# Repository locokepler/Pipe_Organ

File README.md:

# Pipe_Organ
The repository of the code of the pipe organ, over the different iterations

Here is the pipe organ playing Bach's Passacaglia and Fugue in C minor: https://youtu.be/gpJCPvgH33w

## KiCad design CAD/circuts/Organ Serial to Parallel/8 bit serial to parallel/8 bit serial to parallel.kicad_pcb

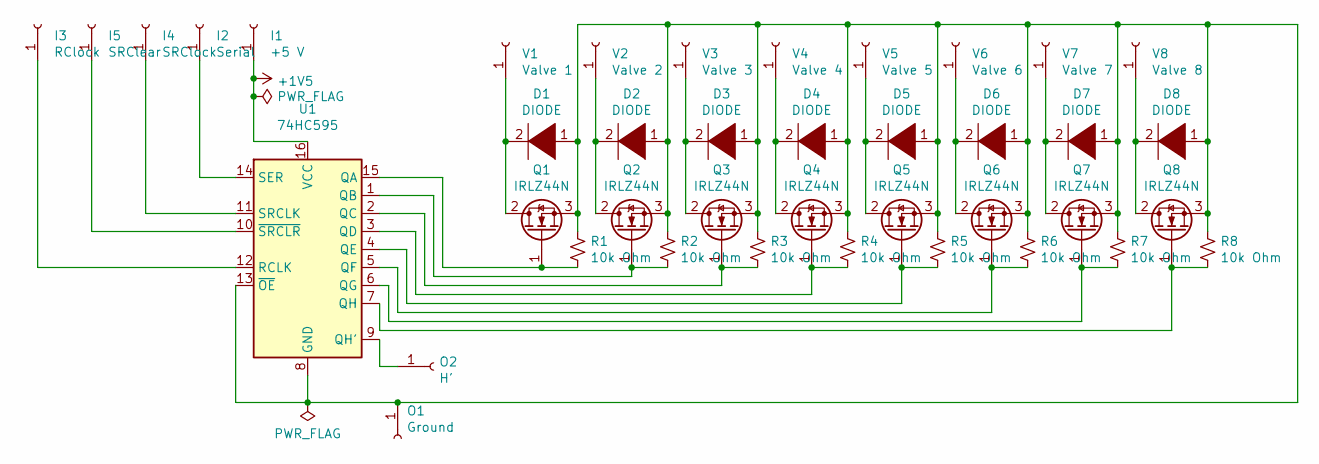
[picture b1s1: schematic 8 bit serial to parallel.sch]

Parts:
D1, D2, D3, D4, D5, D6, D7, D8: DIODE; D_DO-15_P3.81mm_Vertical_AnodeUp
I1: +5 V; SolderWirePad_1x01_Drill2.5mm
I2: Serial; SolderWirePad_1x01_Drill2.5mm
I3: RClock; SolderWirePad_1x01_Drill2.5mm
I4: SRClock; SolderWirePad_1x01_Drill2.5mm
I5: SRClear; SolderWirePad_1x01_Drill2.5mm
O1: Ground; SolderWirePad_1x01_Drill2.5mm
O2: H'; SolderWirePad_1x01_Drill2.5mm
Q1, Q2, Q3, Q4, Q5, Q6, Q7, Q8: IRLZ44N; TO-220-3_Vertical
R1, R2, R3, R4, R5, R6, R7, R8: 10k Ohm; R_Axial_DIN0204_L3.6mm_D1.6mm_P7.62mm_Horizontal
U1: 74HC595; DIP-16_W7.62mm
V1: Valve 1; SolderWirePad_1x01_Drill2.5mm
V2: Valve 2; SolderWirePad_1x01_Drill2.5mm
V3: Valve 3; SolderWirePad_1x01_Drill2.5mm
V4: Valve 4; SolderWirePad_1x01_Drill2.5mm
V5: Valve 5; SolderWirePad_1x01_Drill2.5mm
V6: Valve 6; SolderWirePad_1x01_Drill2.5mm
V7: Valve 7; SolderWirePad_1x01_Drill2.5mm
V8: Valve 8; SolderWirePad_1x01_Drill2.5mm

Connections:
+1V5: I1.1, U1.16 (VCC)
unnamed: D1.1 (K), D2.1 (K), D3.1 (K), D4.1 (K), D5.1 (K), D6.1 (K), D7.1 (K), D8.1 (K), O1.1, Q1.3 (S), Q2.3 (S), Q3.3 (S), Q4.3 (S), Q5.3 (S), Q6.3 (S), Q7.3 (S), Q8.3 (S), R1.1, R2.1, R3.1, R4.1, R5.1, R6.1, R7.1, R8.1, U1.8 (GND), U1.13 (~OE)
unnamed: D1.2 (A), Q1.2 (D), V1.1
unnamed: D2.2 (A), Q2.2 (D), V2.1
unnamed: D3.2 (A), Q3.2 (D), V3.1
unnamed: D4.2 (A), Q4.2 (D), V4.1
unnamed: D5.2 (A), Q5.2 (D), V5.1
unnamed: D6.2 (A), Q6.2 (D), V6.1
unnamed: D7.2 (A), Q7.2 (D), V7.1
unnamed: D8.2 (A), Q8.2 (D), V8.1
unnamed: I2.1, U1.14 (SER)
unnamed: I3.1, U1.12 (RCLK)
unnamed: I4.1, U1.11 (SRCLK)
unnamed: I5.1, U1.10 (~SRCLR)
unnamed: O2.1, U1.9 (QH')
unnamed: Q1.1 (G), R1.2, U1.15 (QA)
unnamed: Q2.1 (G), R2.2, U1.1 (QB)
unnamed: Q3.1 (G), R3.2, U1.2 (QC)
unnamed: Q4.1 (G), R4.2, U1.3 (QD)
unnamed: Q5.1 (G), R5.2, U1.4 (QE)
unnamed: Q6.1 (G), R6.2, U1.5 (QF)
unnamed: Q7.1 (G), R7.2, U1.6 (QG)
unnamed: Q8.1 (G), R8.2, U1.7 (QH)

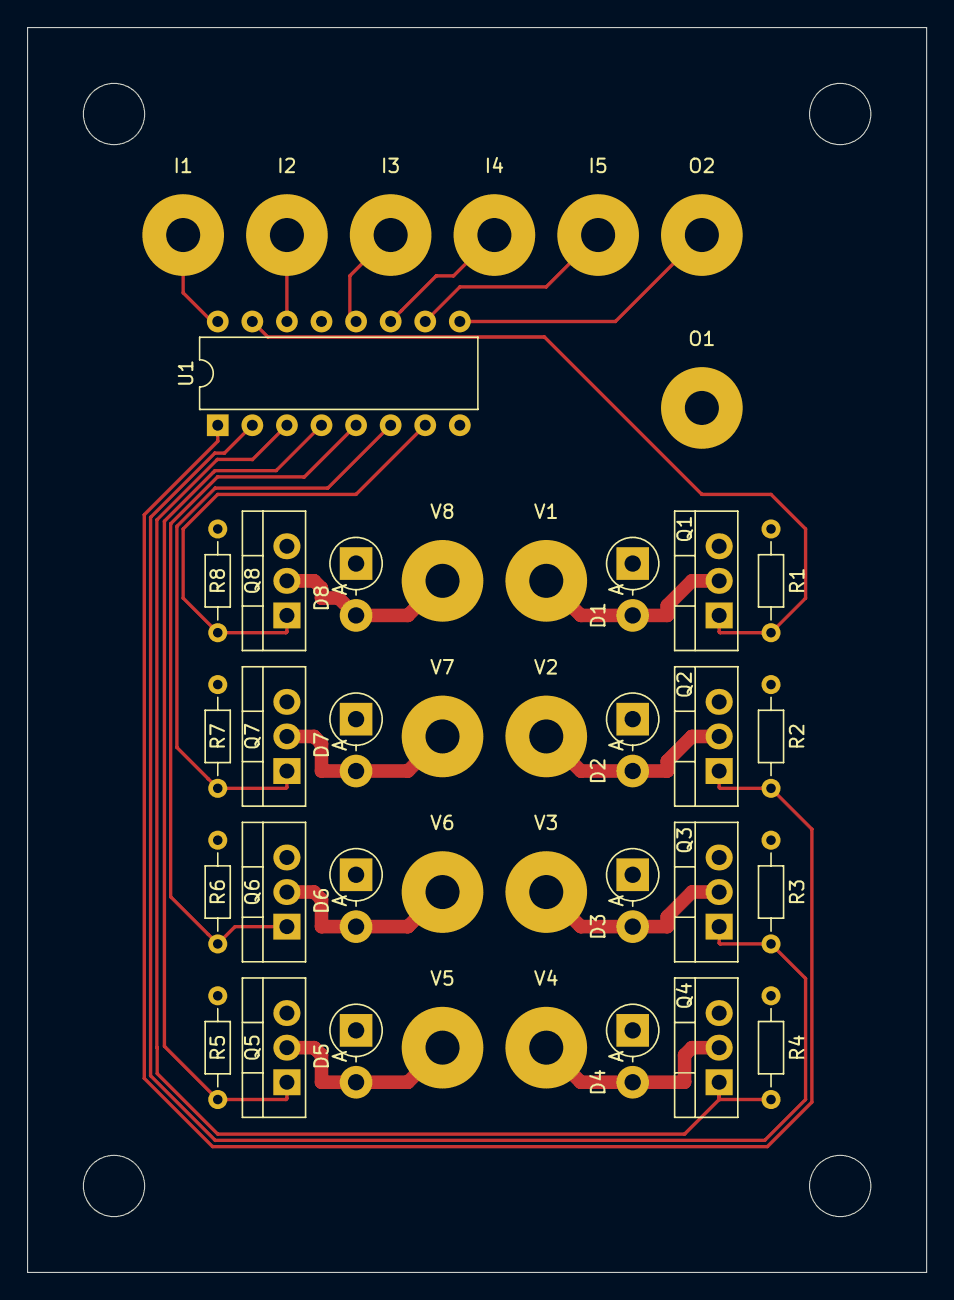
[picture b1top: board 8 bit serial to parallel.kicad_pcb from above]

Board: 2 copper layers, 66.0 x 91.4 mm, 40 parts (0 on the bottom side), 23 nets.

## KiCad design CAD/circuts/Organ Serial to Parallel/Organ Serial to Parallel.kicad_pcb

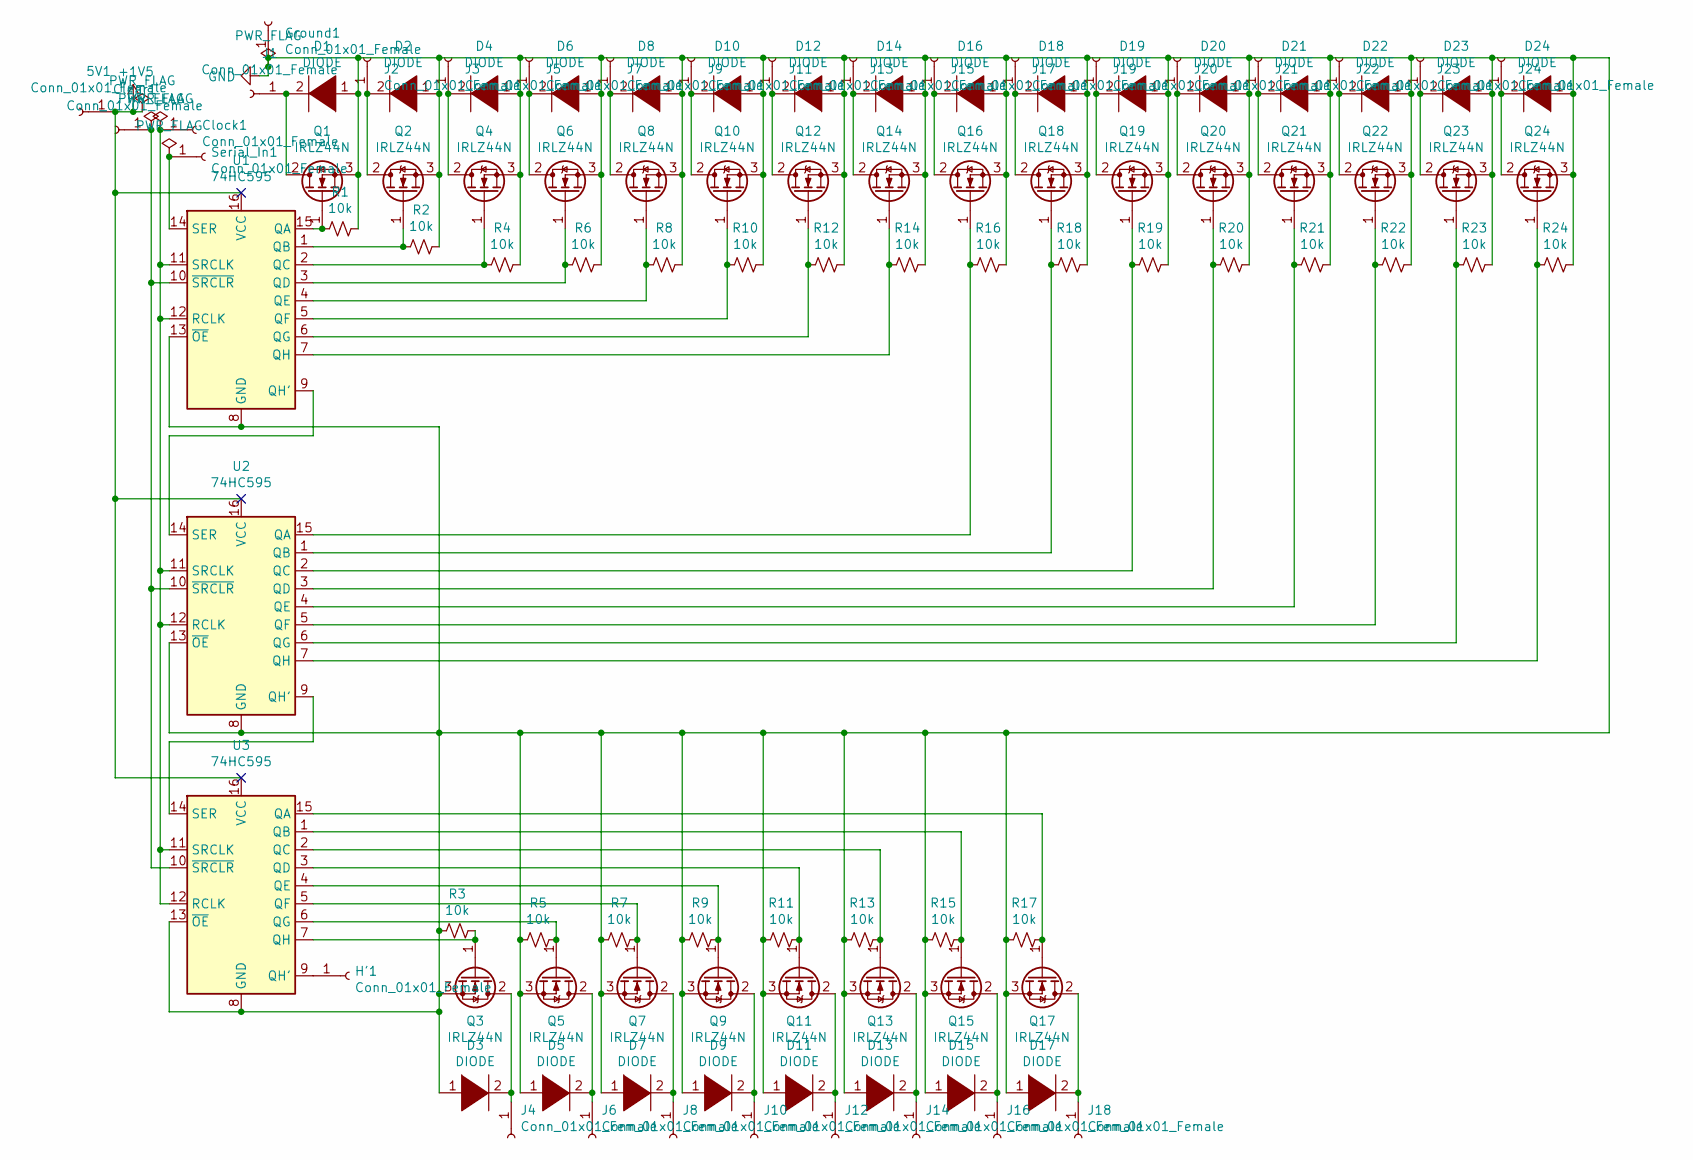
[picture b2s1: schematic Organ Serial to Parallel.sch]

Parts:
5V1: Conn_01x01_Female; PinHeader_1x01_P1.27mm_Vertical
Clear1: Conn_01x01_Female; PinHeader_1x01_P1.27mm_Vertical
Clock1: Conn_01x01_Female; PinHeader_1x01_P1.27mm_Vertical
D1, D2, D3, D4, D5, D6, D7, D8, D9, D10, D11, D12, D13, D14, D15, D16, D17, D18, D19, D20, D21, D22, D23, D24: DIODE; D_A-405_P2.54mm_Vertical_KathodeUp
Ground1: Conn_01x01_Female; PinHeader_1x01_P1.27mm_Vertical
H'1: Conn_01x01_Female; PinHeader_1x01_P1.27mm_Vertical
J1, J2, J3, J4, J5, J6, J7, J8, J9, J10, J11, J12, J13, J14, J15, J16, J17, J18, J19, J20, J21, J22, J23, J24: Conn_01x01_Female; PinHeader_1x01_P1.27mm_Vertical
Q1, Q2, Q3, Q4, Q5, Q6, Q7, Q8, Q9, Q10, Q11, Q12, Q13, Q14, Q15, Q16, Q17, Q18, Q19, Q20, Q21, Q22, Q23, Q24: IRLZ44N; TO-220-3_Vertical
R1, R2, R3, R4, R5, R6, R7, R8, R9, R10, R11, R12, R13, R14, R15, R16, R17, R18, R19, R20, R21, R22, R23, R24: 10k; R_Axial_DIN0309_L9.0mm_D3.2mm_P5.08mm_Vertical
Serial_In1: Conn_01x01_Female; PinHeader_1x01_P1.27mm_Vertical
U1, U2, U3: 74HC595; DIP-16_W7.62mm

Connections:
+1V5: 5V1.1, U1.16 (VCC), U2.16 (VCC), U3.16 (VCC)
GND: D1.1 (K), D2.1 (K), D3.1 (K), D4.1 (K), D5.1 (K), D6.1 (K), D7.1 (K), D8.1 (K), D9.1 (K), D10.1 (K), D11.1 (K), D12.1 (K), D13.1 (K), D14.1 (K), D15.1 (K), D16.1 (K), D17.1 (K), D18.1 (K), D19.1 (K), D20.1 (K), D21.1 (K), D22.1 (K), D23.1 (K), D24.1 (K), Ground1.1, Q1.3 (S), Q2.3 (S), Q3.3 (S), Q4.3 (S), Q5.3 (S), Q6.3 (S), Q7.3 (S), Q8.3 (S), Q9.3 (S), Q10.3 (S), Q11.3 (S), Q12.3 (S), Q13.3 (S), Q14.3 (S), Q15.3 (S), Q16.3 (S), Q17.3 (S), Q18.3 (S), Q19.3 (S), Q20.3 (S), Q21.3 (S), Q22.3 (S), Q23.3 (S), Q24.3 (S), R1.1, R2.1, R3.2, R4.1, R5.2, R6.1, R7.2, R8.1, R9.2, R10.1, R11.2, R12.1, R13.2, R14.1, R15.2, R16.1, R17.2, R18.1, R19.1, R20.1, R21.1, R22.1, R23.1, R24.1, U1.8 (GND), U1.13 (~OE), U2.8 (GND), U2.13 (~OE), U3.8 (GND), U3.13 (~OE)
unnamed: Clear1.1, U1.10 (~SRCLR), U2.10 (~SRCLR), U3.10 (~SRCLR)
unnamed: Clock1.1, U1.11 (SRCLK), U1.12 (RCLK), U2.11 (SRCLK), U2.12 (RCLK), U3.11 (SRCLK), U3.12 (RCLK)
unnamed: D1.2 (A), J1.1, Q1.2 (D)
unnamed: D2.2 (A), J2.1, Q2.2 (D)
unnamed: D3.2 (A), J4.1, Q3.2 (D)
unnamed: D4.2 (A), J3.1, Q4.2 (D)
unnamed: D5.2 (A), J6.1, Q5.2 (D)
unnamed: D6.2 (A), J5.1, Q6.2 (D)
unnamed: D7.2 (A), J8.1, Q7.2 (D)
unnamed: D8.2 (A), J7.1, Q8.2 (D)
unnamed: D9.2 (A), J10.1, Q9.2 (D)
unnamed: D10.2 (A), J9.1, Q10.2 (D)
unnamed: D11.2 (A), J12.1, Q11.2 (D)
unnamed: D12.2 (A), J11.1, Q12.2 (D)
unnamed: D13.2 (A), J14.1, Q13.2 (D)
unnamed: D14.2 (A), J13.1, Q14.2 (D)
unnamed: D15.2 (A), J16.1, Q15.2 (D)
unnamed: D16.2 (A), J15.1, Q16.2 (D)
unnamed: D17.2 (A), J18.1, Q17.2 (D)
unnamed: D18.2 (A), J17.1, Q18.2 (D)
unnamed: D19.2 (A), J19.1, Q19.2 (D)
unnamed: D20.2 (A), J20.1, Q20.2 (D)
unnamed: D21.2 (A), J21.1, Q21.2 (D)
unnamed: D22.2 (A), J22.1, Q22.2 (D)
unnamed: D23.2 (A), J23.1, Q23.2 (D)
unnamed: D24.2 (A), J24.1, Q24.2 (D)
unnamed: H'1.1, U3.9 (QH')
unnamed: Q1.1 (G), R1.2, U1.15 (QA)
unnamed: Q2.1 (G), R2.2, U1.1 (QB)
unnamed: Q3.1 (G), R3.1, U3.7 (QH)
unnamed: Q4.1 (G), R4.2, U1.2 (QC)
unnamed: Q5.1 (G), R5.1, U3.6 (QG)
unnamed: Q6.1 (G), R6.2, U1.3 (QD)
unnamed: Q7.1 (G), R7.1, U3.5 (QF)
unnamed: Q8.1 (G), R8.2, U1.4 (QE)
unnamed: Q9.1 (G), R9.1, U3.4 (QE)
unnamed: Q10.1 (G), R10.2, U1.5 (QF)
unnamed: Q11.1 (G), R11.1, U3.3 (QD)
unnamed: Q12.1 (G), R12.2, U1.6 (QG)
unnamed: Q13.1 (G), R13.1, U3.2 (QC)
unnamed: Q14.1 (G), R14.2, U1.7 (QH)
unnamed: Q15.1 (G), R15.1, U3.1 (QB)
unnamed: Q16.1 (G), R16.2, U2.15 (QA)
unnamed: Q17.1 (G), R17.1, U3.15 (QA)
unnamed: Q18.1 (G), R18.2, U2.1 (QB)
unnamed: Q19.1 (G), R19.2, U2.2 (QC)
unnamed: Q20.1 (G), R20.2, U2.3 (QD)
unnamed: Q21.1 (G), R21.2, U2.4 (QE)
unnamed: Q22.1 (G), R22.2, U2.5 (QF)
unnamed: Q23.1 (G), R23.2, U2.6 (QG)
unnamed: Q24.1 (G), R24.2, U2.7 (QH)
unnamed: Serial_In1.1, U1.14 (SER)
unnamed: U1.9 (QH'), U2.14 (SER)
unnamed: U2.9 (QH'), U3.14 (SER)

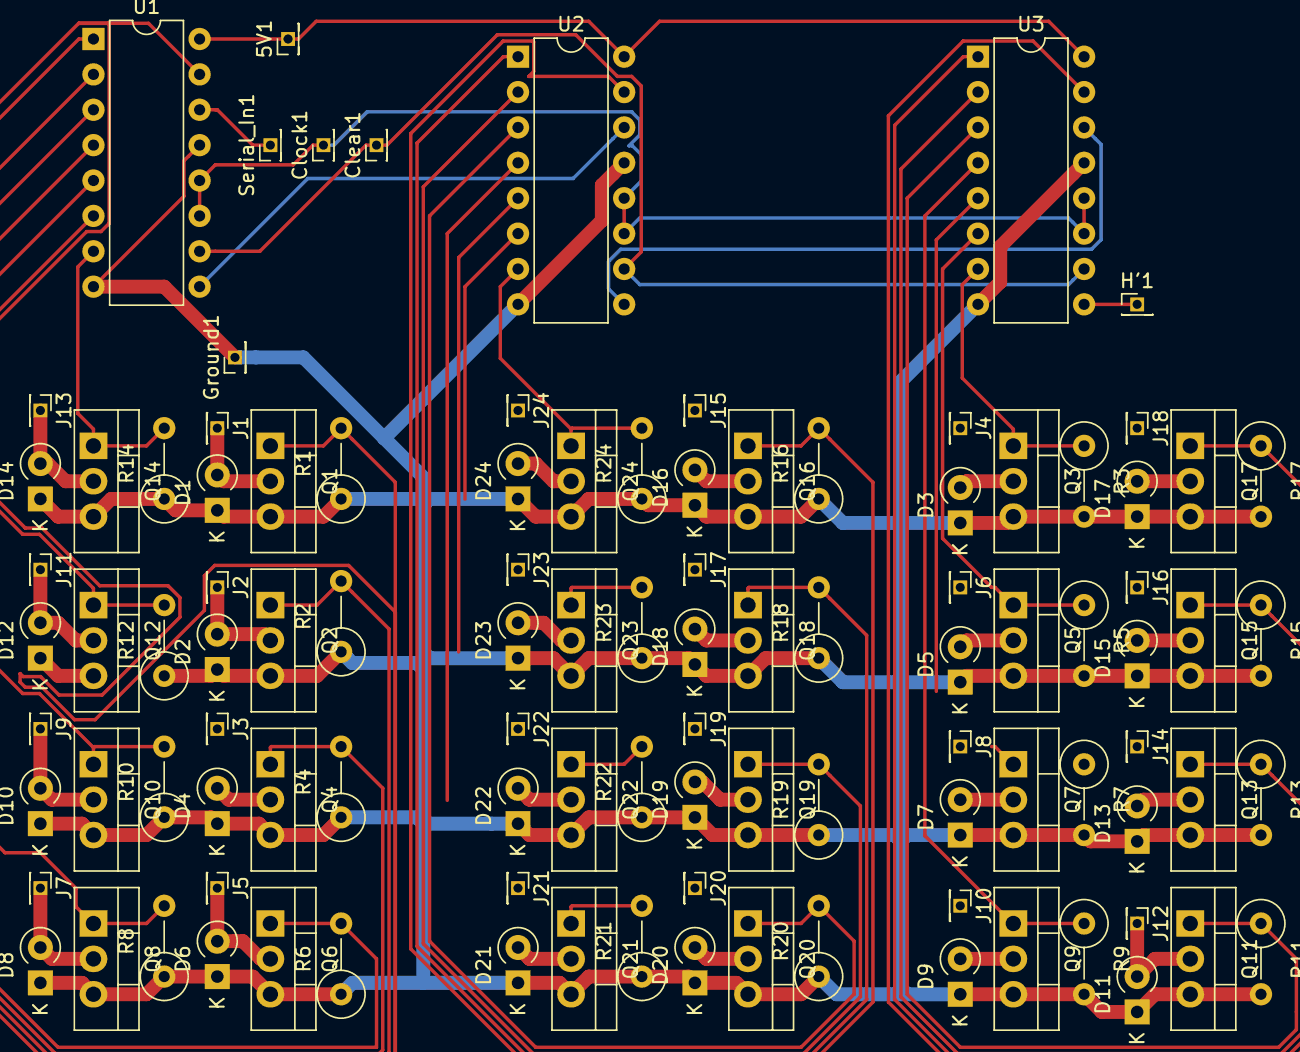
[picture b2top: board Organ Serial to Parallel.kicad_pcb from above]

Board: 2 copper layers, 105 parts (0 on the bottom side), 56 nets.

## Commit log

2020-06-02 Initial versions of organ code, known working
2020-06-02 changing around the way the repository is structured 1
2020-06-02 changing around the structure so code is in its own folder
2020-06-02 compiling but not yet functional, loop not written
2020-06-02 done with loop, however the code is still untested. Also untested is weather the boards will even accept 3.3 V with a Vcc of 5 V
2020-06-02 CAD designs from the organ
2020-06-02 The inventor files for the different whistle designs
2020-06-13 new larger whistles added, first iteration
2020-11-10 better defition of build_rank, compiles
2020-11-10 minor inconsequential change, just removed unnessecessary comment
2021-05-05 current version, operational
2021-05-05 Beginning multichannel control of organ. Each channel should apply to a different stop
2021-05-05 a simple multichannel script as a high likelyhood of working option. Won't have as efficient output as multichannel
